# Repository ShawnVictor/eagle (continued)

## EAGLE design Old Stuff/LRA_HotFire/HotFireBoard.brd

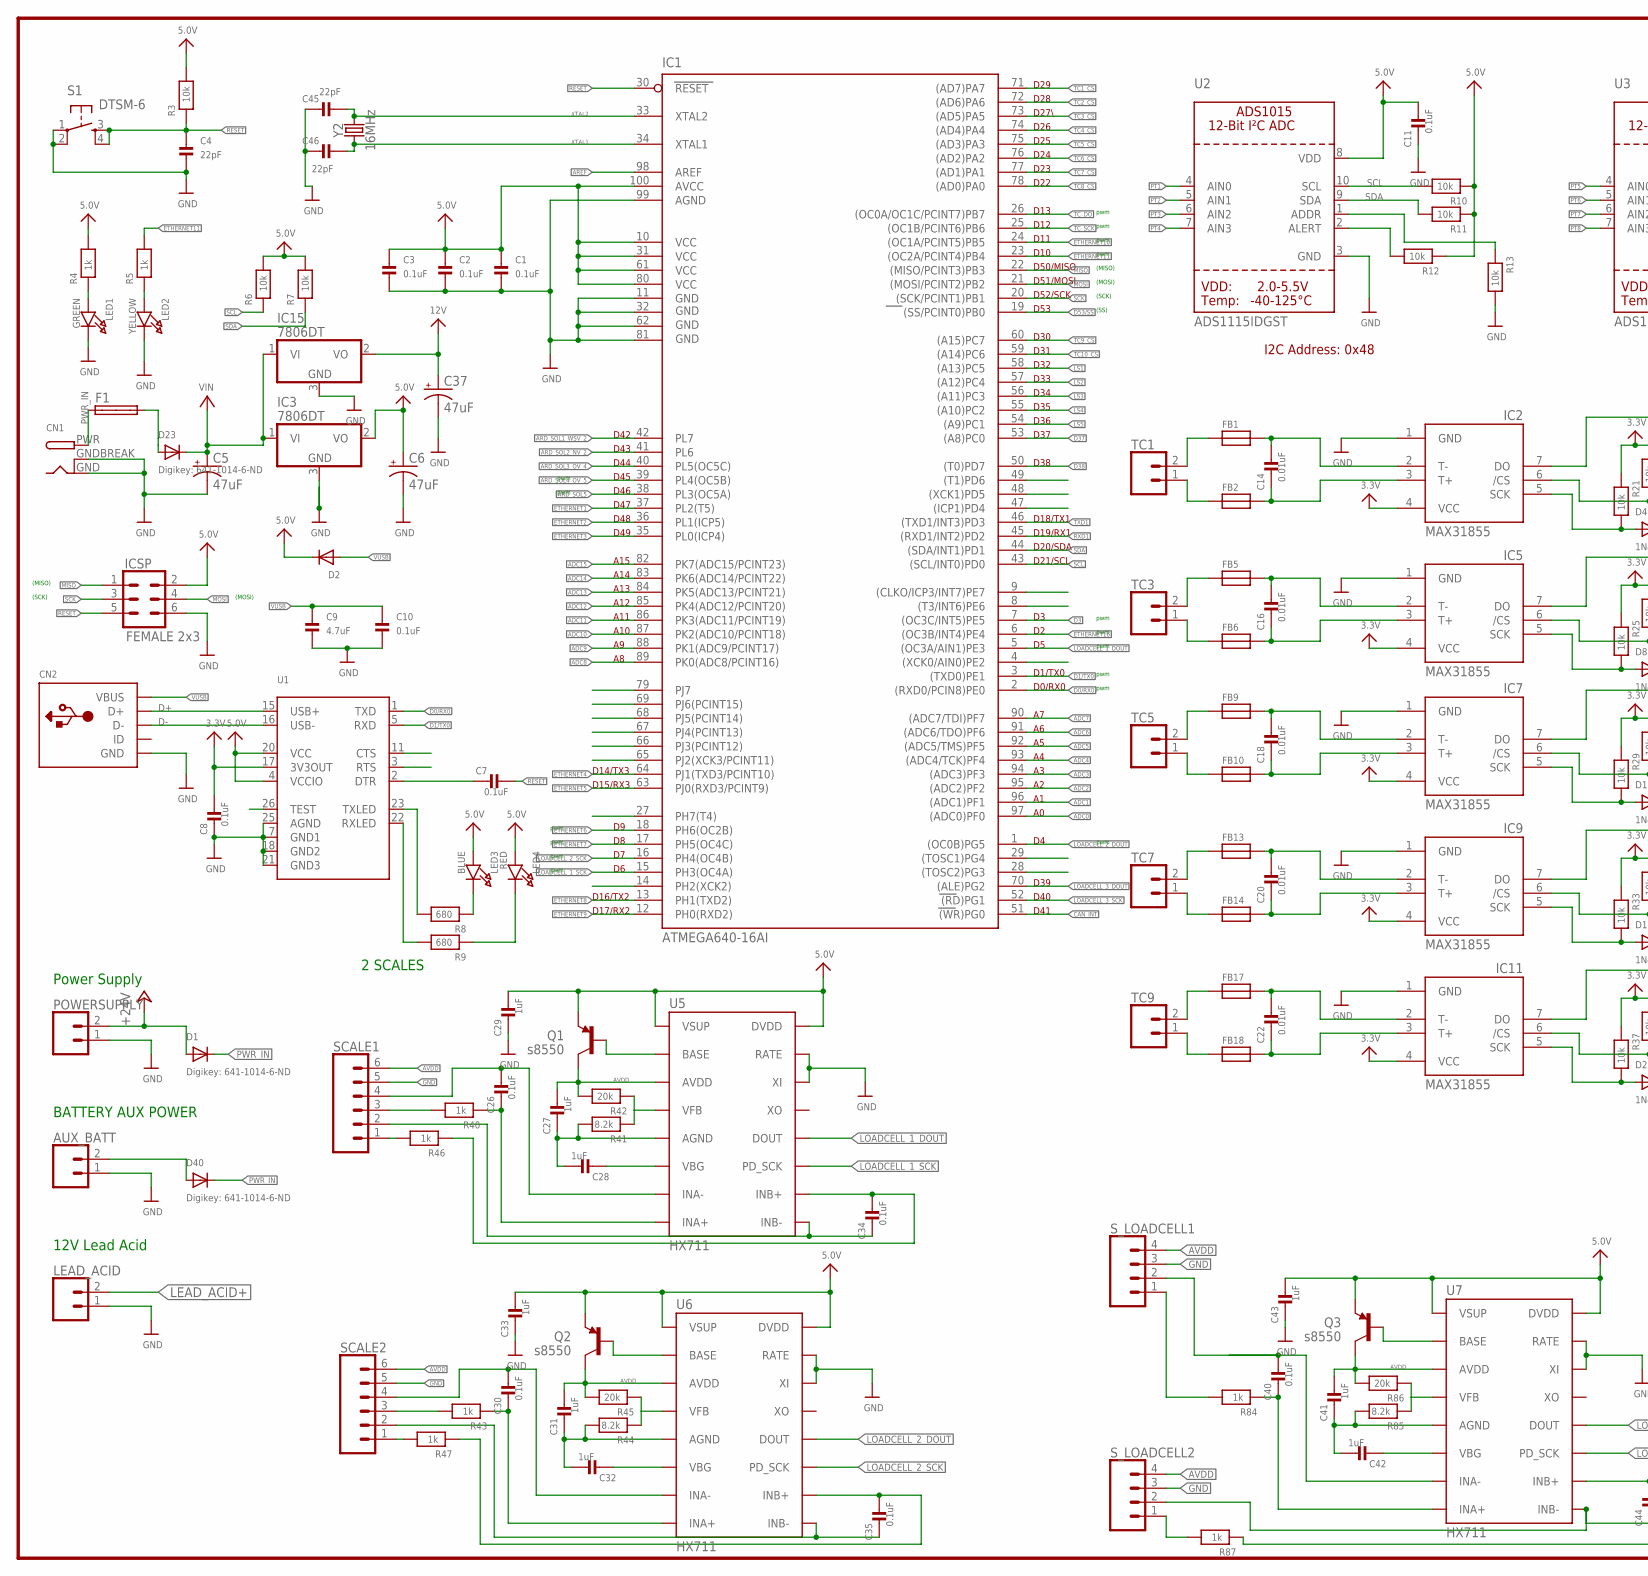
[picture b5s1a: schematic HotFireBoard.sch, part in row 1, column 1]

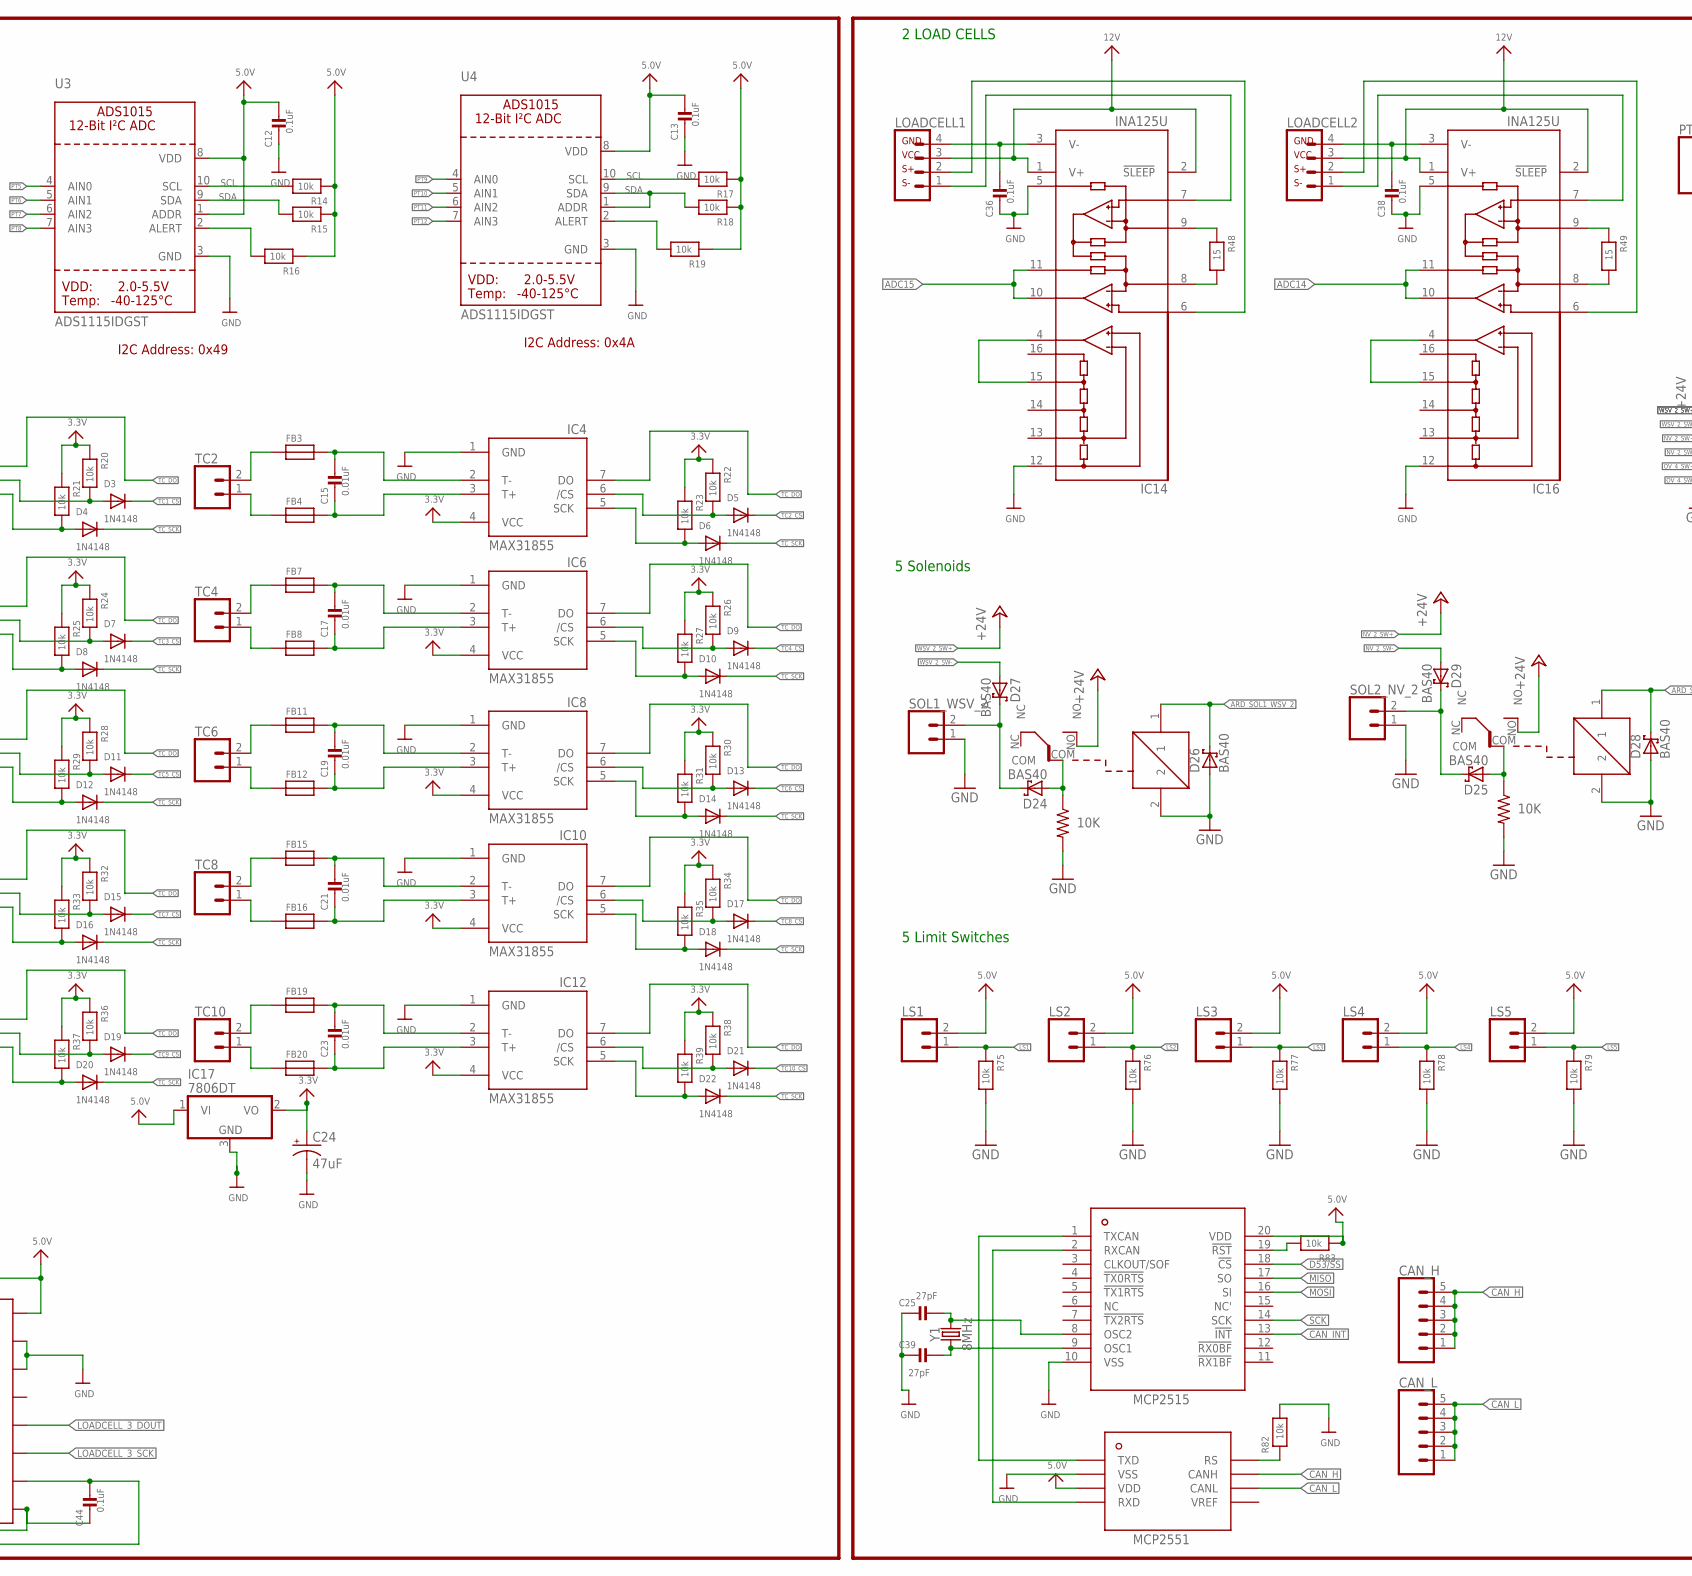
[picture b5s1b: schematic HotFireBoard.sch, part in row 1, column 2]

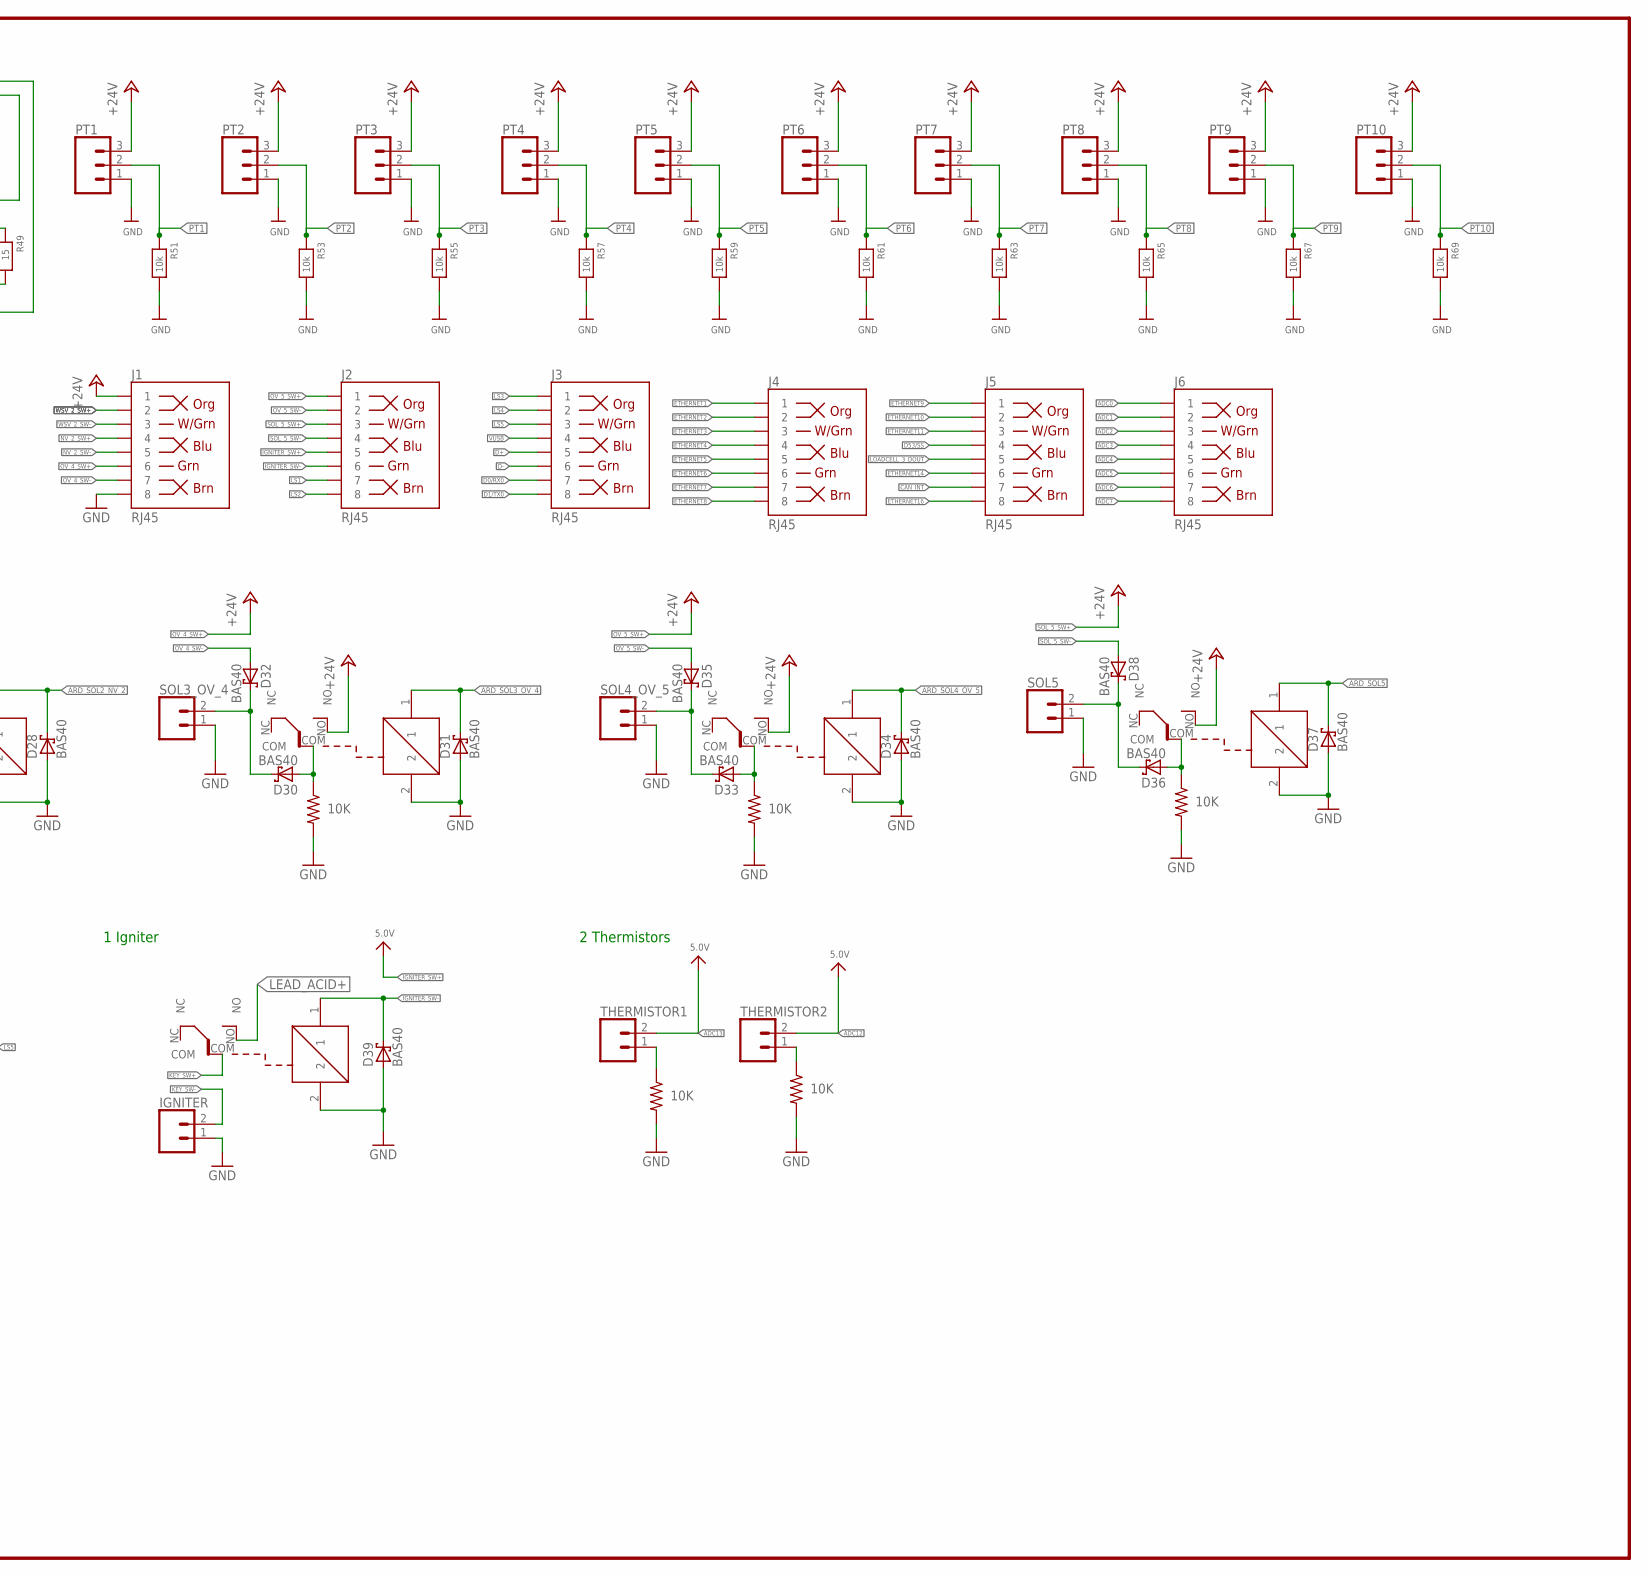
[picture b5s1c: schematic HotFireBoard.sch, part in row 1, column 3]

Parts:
AUX_BATT: CONN_02; 1X02
C1, C2, C3, C7, C8, C10, C11, C12, C13, C26, C30, C34, C35, C36, C38, C40, C44: 0.1uF; 0805
C4, C45, C46: 22pF; 0805
C5, C6, C24, C37: 47uF; PANASONIC_D
C9: 4.7uF; 0805
C14, C15, C16, C17, C18, C19, C20, C21, C22, C23: 0.01uF; 0805
C25, C39: 27pF; 0805
C27, C28, C29, C31, C32, C33, C41, C42, C43: 1uF; 0805
CAN_H: CONN_05SCREW; SCREWTERMINAL-3.5MM-5
CAN_L: CONN_05SCREW; SCREWTERMINAL-3.5MM-5
CN1: DCBARRELPTH; DCJACK_2MM_PTH
CN2: USBMINIB; USB-MINIB
D1, D23, D40: Digikey: 641-1014-6-ND; SMADIODE
D2: DIODESOD-123; SOD-123
D3, D4, D5, D6, D7, D8, D9, D10, D11, D12, D13, D14, D15, D16, D17, D18, D19, D20, D21, D22: 1N4148; SOD-123
D24, D25, D26, D27, D28, D29, D30, D31, D32, D33, D34, D35, D36, D37, D38, D39: BAS40; SOT23
F1: SHK20L
FB1, FB2, FB3, FB4, FB5, FB6, FB7, FB8, FB9, FB10, FB11, FB12, FB13, FB14, FB15, FB16, FB17, FB18, FB19, FB20: FERRITE; 0603
IC1: ATMEGA640-16AI; TQFP100
IC2, IC4, IC5, IC6, IC7, IC8, IC9, IC10, IC11, IC12: MAX31855; SO08
IC3, IC15, IC17: 7806DT; TO252
IC14, IC16: INA125U; SO16-1
ICSP: FEMALE 2x3; 2X3
IGNITER: CONN_02; 1X02
J1, J2, J3, J4, J5, J6: RJ45; RJ45-8
LEAD_ACID: CONN_02; 1X02
LED1: GREEN; CHIPLED_0805
LED2: YELLOW; CHIPLED_0805
LED3: BLUE; CHIPLED_0805
LED4: RED; CHIPLED_0805
LOADCELL1, LOADCELL2: CONN_04; 1X04
LS1, LS2, LS3, LS4, LS5: CONN_02; 1X02
POWERSUPPLY: CONN_02; 1X02
PT1, PT2, PT3, PT4, PT5, PT6, PT7, PT8, PT9, PT10: CONN_03; 1X03
Q1, Q2, Q3: s8550; TO-92
R3, R6, R7, R10, R11, R12, R13, R14, R15, R16, R17, R18, R19, R20, R21, R22, R23, R24, R25, R26, R27, R28, R29, R30, R31, R32, R33, R34, R35, R36, R37, R38, R39, R51, R53, R55, R57, R59, R61, R63, R65, R67, R69, R75, R76, R77, R78, R79, R82, R83: 10k; 0805
R4, R5, R40, R43, R46, R47, R84, R87: 1k; 0805
R8, R9: 680; 0805
R41, R44, R85: 8.2k; 0805
R42, R45, R86: 20k; 0805
R48, R49: 15; 0805
R70, R71, R72, R73, R74, R80, R81: 10K; M0805
S1: DTSM-6
SCALE1, SCALE2: CONN_06SILK_FEMALE_PTH; 1X06
SOL1_WSV_2, SOL2_NV_2, SOL3_OV_4, SOL4_OV_5, SOL5: CONN_02; 1X02
S_LOADCELL1, S_LOADCELL2: CONN_04; 1X04
TC1, TC2, TC3, TC4, TC5, TC6, TC7, TC8, TC9, TC10: CONN_02; 1X02
THERMISTOR1, THERMISTOR2: CONN_025MM; SCREWTERMINAL-5MM-2
U1: FT232RLSSOP28; SSOP28DB
U2, U3, U4: ADS1115IDGST; MSOP10
U5, U6, U7: HX711; SO16
U$6: MCP2515; TSSOP20
U$7: MCP2551; SOIC-8
U$128, U$129, U$130, U$131, U$132, U$138: RW-SH
Y1: 8MHz; HC49US
Y2: 16MHz; HC49US

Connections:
3.3V: C8.2, C24.+, IC2.4 (VCC), IC4.4 (VCC), IC5.4 (VCC), IC6.4 (VCC), IC7.4 (VCC), IC8.4 (VCC), IC9.4 (VCC), IC10.4 (VCC), IC11.4 (VCC), IC12.4 (VCC), IC17.2 (VO), R20.1, R21.1, R22.1, R23.1, R24.1, R25.1, R26.1, R27.1, R28.1, R29.1, R30.1, R31.1, R32.1, R33.1, R34.1, R35.1, R36.1, R37.1, R38.1, R39.1, U1.17 (3V3OUT)
5.0V: C1.1, C2.1, C3.1, C6.+, C11.2, C12.2, C13.2, C29.2, C33.2, C43.2, D2.C, IC1.10 (VCC), IC1.31 (VCC1), IC1.61 (VCC2), IC1.80 (VCC3), IC1.100 (AVCC), IC3.2 (VO), IC17.1 (VI), ICSP.2, LED3.A, LED4.A, LS1.2, LS2.2, LS3.2, LS4.2, LS5.2, Q1.1 (E), Q2.1 (E), Q3.1 (E), R3.2, R4.2, R6.2, R7.2, R10.1, R11.1, R12.1, R14.1, R15.1, R16.1, R17.1, R18.1, R19.1, R83.1, U1.4 (VCCIO), U1.20 (VCC), U2.8 (VDD), U3.1 (ADDR), U3.8 (VDD), U4.8 (VDD), U5.1 (VSUP), U5.16 (DVDD), U6.1 (VSUP), U6.16 (DVDD), U7.1 (VSUP), U7.16 (DVDD), U$6.20 (VDD), U$7.VDD
12V: C37.+, IC14.1 (V+), IC14.2 (!SLEEP), IC15.2 (VO), IC16.1 (V+), IC16.2 (!SLEEP), LOADCELL1.3, LOADCELL2.3
+24V: D1.A, J1.1, POWERSUPPLY.2, PT1.3, PT2.3, PT3.3, PT4.3, PT5.3, PT6.3, PT7.3, PT8.3, PT9.3, PT10.3, U$128.NO, U$129.NO, U$130.NO, U$131.NO, U$132.NO
ADC0: IC1.97 ((ADC0)PF0), J6.1
ADC1: IC1.96 ((ADC1)PF1), J6.2
ADC2: IC1.95 ((ADC2)PF2), J6.3
ADC3: IC1.94 ((ADC3)PF3), J6.4
ADC4: IC1.93 ((ADC4/TCK)PF4), J6.5
ADC5: IC1.92 ((ADC5/TMS)PF5), J6.6
ADC6: IC1.91 ((ADC6/TDO)PF6), J6.7
ADC7: IC1.90 ((ADC7/TDI)PF7), J6.8
ADC8: IC1.89 (PK0(ADC8/PCINT16))
ADC9: IC1.88 (PK1(ADC9/PCINT17))
ADC10: IC1.87 (PK2(ADC10/PCINT18))
ADC11: IC1.86 (PK3(ADC11/PCINT19))
ADC12: IC1.85 (PK4(ADC12/PCINT20)), THERMISTOR2.2
ADC13: IC1.84 (PK5(ADC13/PCINT21)), THERMISTOR1.2
ADC14: IC1.83 (PK6(ADC14/PCINT22)), IC16.10 (OUT), IC16.11 (SENSE)
ADC15: IC1.82 (PK7(ADC15/PCINT23)), IC14.10 (OUT), IC14.11 (SENSE)
ARD_SOL1_WSV_2: D26.3 (C), IC1.42 (PL7), U$128.1
ARD_SOL2_NV_2: D28.3 (C), IC1.41 (PL6), U$129.1
ARD_SOL3_OV_4: D31.3 (C), IC1.40 (PL5(OC5C)), U$130.1
ARD_SOL4_OV_5: D34.3 (C), IC1.39 (PL4(OC5B)), U$131.1
ARD_SOL5: D37.3 (C), IC1.38 (PL3(OC5A)), U$132.1
AREF: IC1.98 (AREF)
AVDD: C27.2, C31.2, C41.2, Q1.3 (C), Q2.3 (C), Q3.3 (C), R42.2, R45.2, R86.2, SCALE1.6, SCALE2.6, S_LOADCELL1.4, S_LOADCELL2.4, U5.3 (AVDD), U6.3 (AVDD), U7.3 (AVDD)
CAN_H: CAN_H.1, CAN_H.2, CAN_H.3, CAN_H.4, CAN_H.5, U$7.CANH
CAN_INT: IC1.51 ((WR)PG0), J5.7, U$6.13 (!INT)
CAN_L: CAN_L.1, CAN_L.2, CAN_L.3, CAN_L.4, CAN_L.5, U$7.CANL
D0/RX0: IC1.2 ((RXD0/PCIN8)PE0), J3.7, U1.1 (TXD)
D1/TX0: IC1.3 ((TXD0)PE1), J3.8, U1.5 (RXD)
D3: IC1.7 ((OC3C/INT5)PE5)
D37: IC1.53 ((A8)PC0)
D38: IC1.50 ((T0)PD7)
D53/SS: IC1.19 ((SS/PCINT0)PB0), J5.4, U$6.18 (!CS)
D+: CN2.D+, J3.5, U1.15 (USB+)
D-: CN2.D-, J3.6, U1.16 (USB-)
ETHERNET1: IC1.37 (PL2(T5)), J4.1
ETHERNET2: IC1.36 (PL1(ICP5)), J4.2
ETHERNET3: IC1.35 (PL0(ICP4)), J4.3
ETHERNET4: IC1.64 (PJ1(TXD3/PCINT10)), J4.4
ETHERNET5: IC1.63 (PJ0(RXD3/PCINT9)), J4.5
ETHERNET6: IC1.18 (PH6(OC2B)), J4.6
ETHERNET7: IC1.17 (PH5(OC4C)), J4.7
ETHERNET8: IC1.13 (PH1(TXD2)), J4.8
ETHERNET9: IC1.12 (PH0(RXD2)), J5.1
ETHERNET10: IC1.24 ((OC1A/PCINT5)PB5), J5.2
ETHERNET11: IC1.23 ((OC2A/PCINT4)PB4), J5.3, R5.2
ETHERNET14: J5.6
ETHERNET16: IC1.6 ((OC3B/INT4)PE4), J5.8
GND: AUX_BATT.1, C1.2, C2.2, C3.2, C4.2, C5.-, C6.-, C8.1, C9.1, C10.1, C11.1, C12.1, C13.1, C24.-, C25.1, C29.1, C33.1, C36.1, C37.-, C38.1, C39.1, C43.1, C45.1, C46.1, CN1.GND, CN1.GNDBREAK, CN2.GND, D26.1 (A), D28.1 (A), D31.1 (A), D34.1 (A), D37.1 (A), D39.1 (A), IC1.11 (GND), IC1.32 (GND1), IC1.62 (GND2), IC1.81 (GND3), IC1.99 (AGND), IC2.1 (GND), IC3.3 (GND), IC4.1 (GND), IC5.1 (GND), IC6.1 (GND), IC7.1 (GND), IC8.1 (GND), IC9.1 (GND), IC10.1 (GND), IC11.1 (GND), IC12.1 (GND), IC14.5 (REF), IC14.12 (REFCOM), IC15.3 (GND), IC16.5 (REF), IC16.12 (REFCOM), IC17.3 (GND), ICSP.6, IGNITER.1, J1.8, LEAD_ACID.1, LED1.C, LED2.C, POWERSUPPLY.1, PT1.1, PT2.1, PT3.1, PT4.1, PT5.1, PT6.1, PT7.1, PT8.1, PT9.1, PT10.1, R13.2, R51.2, R53.2, R55.2, R57.2, R59.2, R61.2, R63.2, R65.2, R67.2, R69.2, R70.2, R71.2, R72.2, R73.2, R74.2, R75.2, R76.2, R77.2, R78.2, R79.2, R80.2, R81.2, R82.2, S1.1, S1.2, SCALE1.5, SCALE2.5, SOL1_WSV_2.1, SOL2_NV_2.1, SOL3_OV_4.1, SOL4_OV_5.1, SOL5.1, S_LOADCELL1.3, S_LOADCELL2.3, U1.7 (GND1), U1.18 (GND2), U1.21 (GND3), U1.25 (AGND), U2.3 (GND), U3.3 (GND), U4.3 (GND), U5.14 (XI), U5.15 (RATE), U6.14 (XI), U6.15 (RATE), U7.14 (XI), U7.15 (RATE), U$6.10 (VSS), U$7.VSS, U$128.2, U$129.2, U$130.2, U$131.2, U$132.2, U$138.2
IGNITER_SW+: J2.5
IGNITER_SW-: D39.3 (C), J2.6, U$138.1
KEY_SW+: U$138.COM
KEY_SW-: IGNITER.2
LEAD_ACID+: LEAD_ACID.2, U$138.NO
LOADCELL_1_DOUT: IC1.5 ((OC3A/AIN1)PE3), U5.12 (DOUT)
LOADCELL_1_SCK: IC1.15 (PH3(OC4A)), U5.11 (PD_SCK)
LOADCELL_2_DOUT: IC1.1 ((OC0B)PG5), U6.12 (DOUT)
LOADCELL_2_SCK: IC1.16 (PH4(OC4B)), U6.11 (PD_SCK)
LOADCELL_3_DOUT: IC1.70 ((ALE)PG2), J5.5, U7.12 (DOUT)
LOADCELL_3_SCK: IC1.52 ((RD)PG1), U7.11 (PD_SCK)
LS1: IC1.58 ((A13)PC5), J2.7, LS1.1, R75.1
LS2: IC1.57 ((A12)PC4), J2.8, LS2.1, R76.1
LS3: IC1.56 ((A11)PC3), J3.1, LS3.1, R77.1
LS4: IC1.55 ((A10)PC2), J3.2, LS4.1, R78.1
LS5: IC1.54 ((A9)PC1), J3.3, LS5.1, R79.1
MISO: IC1.22 ((MISO/PCINT3)PB3), ICSP.1, U$6.17 (SO)
MOSI: IC1.21 ((MOSI/PCINT2)PB2), ICSP.4, U$6.16 (SI)
unnamed: U$6.1 (TXCAN), U$7.TXD
unnamed: U$6.2 (RXCAN), U$7.RXD
unnamed: C25.2, U$6.8 (OSC2), Y1.2
unnamed: LED1.A, R4.1
unnamed: LED2.A, R5.1
unnamed: LED3.C, R8.1
unnamed: R9.2, U1.22 (RXLED)
unnamed: R8.2, U1.23 (TXLED)
unnamed: LED4.C, R9.1
unnamed: C14.1, FB2.2, IC2.3 (T+)
unnamed: C7.1, U1.2 (DTR)
unnamed: C14.2, FB1.2, IC2.2 (T-)
unnamed: R82.1, U$7.RS
unnamed: D3.A, IC2.6 (/CS), R20.2
unnamed: R83.2, U$6.19 (!RST)
unnamed: C39.2, U$6.9 (OSC1), Y1.1
unnamed: R84.2, S_LOADCELL1.1
unnamed: R12.2, U2.2 (ALERT)
unnamed: C40.1, R84.1, U7.8 (INA+)
unnamed: R16.2, U3.2 (ALERT)
unnamed: R13.1, U2.1 (ADDR)
unnamed: C40.2, S_LOADCELL1.2, U7.7 (INA-)
unnamed: FB1.1, TC1.2
unnamed: R19.2, U4.2 (ALERT)
unnamed: C41.1, C42.2, R85.2, U7.5 (AGND)
unnamed: FB2.1, TC1.1
unnamed: D4.A, IC2.5 (SCK), R21.2
unnamed: C15.2, FB3.2, IC4.2 (T-)
unnamed: C42.1, U7.6 (VBG)
unnamed: R85.1, R86.1, U7.4 (VFB)
unnamed: C15.1, FB4.2, IC4.3 (T+)
unnamed: FB3.1, TC2.2
unnamed: FB4.1, TC2.1
unnamed: D5.A, IC4.6 (/CS), R22.2
unnamed: D6.A, IC4.5 (SCK), R23.2
unnamed: C16.2, FB5.2, IC5.2 (T-)
unnamed: C16.1, FB6.2, IC5.3 (T+)
unnamed: FB5.1, TC3.2
unnamed: FB6.1, TC3.1
unnamed: D7.A, IC5.6 (/CS), R24.2
unnamed: D8.A, IC5.5 (SCK), R25.2
unnamed: C17.2, FB7.2, IC6.2 (T-)
unnamed: C17.1, FB8.2, IC6.3 (T+)
unnamed: FB7.1, TC4.2
unnamed: FB8.1, TC4.1
unnamed: D9.A, IC6.6 (/CS), R26.2
unnamed: D10.A, IC6.5 (SCK), R27.2
unnamed: C18.2, FB9.2, IC7.2 (T-)
unnamed: C18.1, FB10.2, IC7.3 (T+)
unnamed: FB9.1, TC5.2
unnamed: FB10.1, TC5.1
unnamed: D11.A, IC7.6 (/CS), R28.2
unnamed: D12.A, IC7.5 (SCK), R29.2
unnamed: C19.2, FB11.2, IC8.2 (T-)
unnamed: C19.1, FB12.2, IC8.3 (T+)
unnamed: FB11.1, TC6.2
unnamed: FB12.1, TC6.1
unnamed: D13.A, IC8.6 (/CS), R30.2
unnamed: D14.A, IC8.5 (SCK), R31.2
unnamed: C20.2, FB13.2, IC9.2 (T-)
unnamed: C20.1, FB14.2, IC9.3 (T+)
unnamed: FB13.1, TC7.2
unnamed: FB14.1, TC7.1
unnamed: D15.A, IC9.6 (/CS), R32.2
unnamed: D16.A, IC9.5 (SCK), R33.2
unnamed: C21.2, FB15.2, IC10.2 (T-)
unnamed: C21.1, FB16.2, IC10.3 (T+)
unnamed: FB15.1, TC8.2
unnamed: FB16.1, TC8.1
unnamed: D17.A, IC10.6 (/CS), R34.2
unnamed: D18.A, IC10.5 (SCK), R35.2
unnamed: C22.2, FB17.2, IC11.2 (T-)
unnamed: C22.1, FB18.2, IC11.3 (T+)
unnamed: FB17.1, TC9.2
unnamed: FB18.1, TC9.1
unnamed: D19.A, IC11.6 (/CS), R36.2
unnamed: D20.A, IC11.5 (SCK), R37.2
unnamed: C23.2, FB19.2, IC12.2 (T-)
unnamed: C23.1, FB20.2, IC12.3 (T+)
unnamed: FB19.1, TC10.2
unnamed: FB20.1, TC10.1
unnamed: D21.A, IC12.6 (/CS), R38.2
unnamed: D22.A, IC12.5 (SCK), R39.2
unnamed: R40.2, SCALE1.3
unnamed: C26.1, R40.1, U5.8 (INA+)
unnamed: C26.2, SCALE1.4, U5.7 (INA-)
unnamed: R43.2, SCALE2.3
unnamed: C27.1, C28.2, R41.2, U5.5 (AGND)
unnamed: C28.1, U5.6 (VBG)
unnamed: R41.1, R42.1, U5.4 (VFB)
unnamed: Q1.2 (B), U5.2 (BASE)
unnamed: C30.1, R43.1, U6.8 (INA+)
unnamed: C30.2, SCALE2.4, U6.7 (INA-)
unnamed: C31.1, C32.2, R44.2, U6.5 (AGND)
unnamed: C32.1, U6.6 (VBG)
unnamed: R44.1, R45.1, U6.4 (VFB)
unnamed: Q2.2 (B), U6.2 (BASE)
unnamed: C34.1, SCALE1.2, U5.9 (INB-)
unnamed: C34.2, R46.1, U5.10 (INB+)
unnamed: R46.2, SCALE1.1
unnamed: C35.1, SCALE2.2, U6.9 (INB-)
unnamed: C35.2, R47.1, U6.10 (INB+)
unnamed: R47.2, SCALE2.1
unnamed: C36.2, IC14.3 (V-), LOADCELL1.4
unnamed: C38.2, IC16.3 (V-), LOADCELL2.4
unnamed: IC14.9 (RG), R48.1
unnamed: IC14.8 (RG), R48.2
unnamed: IC14.6 (+IN), LOADCELL1.2
unnamed: IC16.9 (RG), R49.1
unnamed: IC16.8 (RG), R49.2
unnamed: IC16.6 (+IN), LOADCELL2.2
unnamed: IC14.4 (REFOUT), IC14.15 (REF5)
unnamed: IC14.7 (-IN), LOADCELL1.1
unnamed: IC16.4 (REFOUT), IC16.15 (REF5)
unnamed: IC16.7 (-IN), LOADCELL2.1
unnamed: D24.3 (C), D27.3 (C), SOL1_WSV_2.2
unnamed: D24.1 (A), R70.1, U$128.COM
unnamed: D25.3 (C), D29.3 (C), SOL2_NV_2.2
unnamed: D25.1 (A), R71.1, U$129.COM
unnamed: D30.3 (C), D32.3 (C), SOL3_OV_4.2
unnamed: D30.1 (A), R72.1, U$130.COM
unnamed: D33.3 (C), D35.3 (C), SOL4_OV_5.2
unnamed: D33.1 (A), R73.1, U$131.COM
unnamed: D36.3 (C), D38.3 (C), SOL5.2
unnamed: D36.1 (A), R74.1, U$132.COM
unnamed: R80.1, THERMISTOR1.1
unnamed: Q3.2 (B), U7.2 (BASE)
unnamed: C44.1, S_LOADCELL2.2, U7.9 (INB-)
unnamed: R81.1, THERMISTOR2.1
unnamed: C44.2, R87.1, U7.10 (INB+)
unnamed: R87.2, S_LOADCELL2.1
unnamed: D23.A, F1.2A
unnamed: AUX_BATT.2, D40.A
NV_2_SW+: J1.4
NV_2_SW-: D29.1 (A), J1.5
OV_4_SW+: J1.6
OV_4_SW-: D32.1 (A), J1.7
OV_5_SW+: J2.1
OV_5_SW-: D35.1 (A), J2.2
PT1: PT1.2, R51.1, U2.4 (AIN0)
PT2: PT2.2, R53.1, U2.5 (AIN1)
PT3: PT3.2, R55.1, U2.6 (AIN2)
PT4: PT4.2, R57.1, U2.7 (AIN3)
PT5: PT5.2, R59.1, U3.4 (AIN0)
PT6: PT6.2, R61.1, U3.5 (AIN1)
PT7: PT7.2, R63.1, U3.6 (AIN2)
PT8: PT8.2, R65.1, U3.7 (AIN3)
PT9: PT9.2, R67.1, U4.4 (AIN0)
PT10: PT10.2, R69.1, U4.5 (AIN1)
PT11: U4.6 (AIN2)
PT12: U4.7 (AIN3)
PWR_IN: CN1.PWR, D1.C, D40.C, F1.1A
RESET: C4.1, C7.2, IC1.30 (RESET), ICSP.5, R3.1, S1.3, S1.4
RXD1: IC1.45 ((RXD1/INT2)PD2)
SCK: IC1.20 ((SCK/PCINT1)PB1), ICSP.3, U$6.14 (SCK)
SCL: IC1.43 ((SCL/INT0)PD0), R6.1, R10.2, R14.2, R17.2, U2.10 (SCL), U3.10 (SCL), U4.10 (SCL)
SDA: IC1.44 ((SDA/INT1)PD1), R7.1, R11.2, R15.2, R18.2, U2.9 (SDA), U3.9 (SDA), U4.1 (ADDR), U4.9 (SDA)
SOL_5_SW+: J2.3
SOL_5_SW-: D38.1 (A), J2.4
TC1_CS: D3.C, IC1.71 ((AD7)PA7)
TC2_CS: D5.C, IC1.72 ((AD6)PA6)
TC3_CS: D7.C, IC1.73 ((AD5)PA5)
TC4_CS: D9.C, IC1.74 ((AD4)PA4)
TC5_CS: D11.C, IC1.75 ((AD3)PA3)
TC6_CS: D13.C, IC1.76 ((AD2)PA2)
TC7_CS: D15.C, IC1.77 ((AD1)PA1)
TC8_CS: D17.C, IC1.78 ((AD0)PA0)
TC9_CS: D19.C, IC1.60 ((A15)PC7)
TC10_CS: D21.C, IC1.59 ((A14)PC6)
TC_DO: IC1.26 ((OC0A/OC1C/PCINT7)PB7), IC2.7 (DO), IC4.7 (DO), IC5.7 (DO), IC6.7 (DO), IC7.7 (DO), IC8.7 (DO), IC9.7 (DO), IC10.7 (DO), IC11.7 (DO), IC12.7 (DO)
TC_SCK: D4.C, D6.C, D8.C, D10.C, D12.C, D14.C, D16.C, D18.C, D20.C, D22.C, IC1.25 ((OC1B/PCINT6)PB6)
TXD1: IC1.46 ((TXD1/INT3)PD3)
VIN: C5.+, D23.C, IC3.1 (VI), IC15.1 (VI)
VUSB: C9.2, C10.2, CN2.VBUS, D2.A, J3.4
WSV_2_SW+: J1.2
WSV_2_SW-: D27.1 (A), J1.3
XTAL1: C46.2, IC1.34 (XTAL1), Y2.1
XTAL2: C45.2, IC1.33 (XTAL2), Y2.2

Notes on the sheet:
pwm
(SS)
(SCK)
(MOSI)
(MISO)
I2C Address: 0x48
I2C Address: 0x49
I2C Address: 0x4A
BATTERY AUX POWER
5 Solenoids
5 Limit Switches
1 Igniter
2 SCALES
2 Thermistors
GND
VCC
2 LOAD CELLS
D42
D43
D44
D45
D46
D47
D48
D49
A15
A14
A13
A12
A11
A10
D14/TX3
D15/RX3
D16/TX2
D17/RX2
D29
D28
D27\
D26
D25

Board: 2 copper layers, 276 parts (0 on the bottom side), 227 nets, no tracks yet.

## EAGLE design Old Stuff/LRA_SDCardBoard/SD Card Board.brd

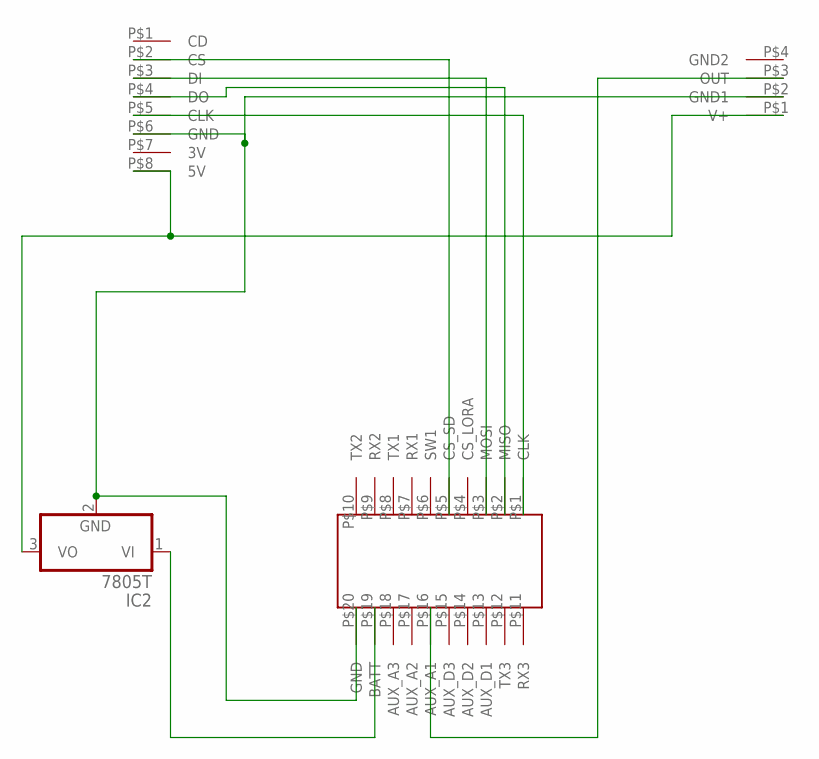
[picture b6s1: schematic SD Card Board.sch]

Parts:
IC2: 7805T; TO220H
U$1: SMALLHEADERPACKAGE
U$2: SDCARDREADER; SDCARDBOARD
U$3: THERMOCOUPLE; THERMOBOARD

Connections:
unnamed: IC2.1 (VI), U$1.P$19 (BATT)
unnamed: IC2.3 (VO), U$2.P$8 (5V), U$3.P$1 (V+)
unnamed: IC2.2 (GND), U$1.P$20 (GND), U$2.P$6 (GND), U$3.P$2 (GND1)
unnamed: U$1.P$1 (CLK), U$2.P$5 (CLK)
unnamed: U$1.P$16 (AUX_A1), U$3.P$3 (OUT)
unnamed: U$1.P$2 (MISO), U$2.P$4 (DO)
unnamed: U$1.P$3 (MOSI), U$2.P$3 (DI)
unnamed: U$1.P$5 (CS_SD), U$2.P$2 (CS)

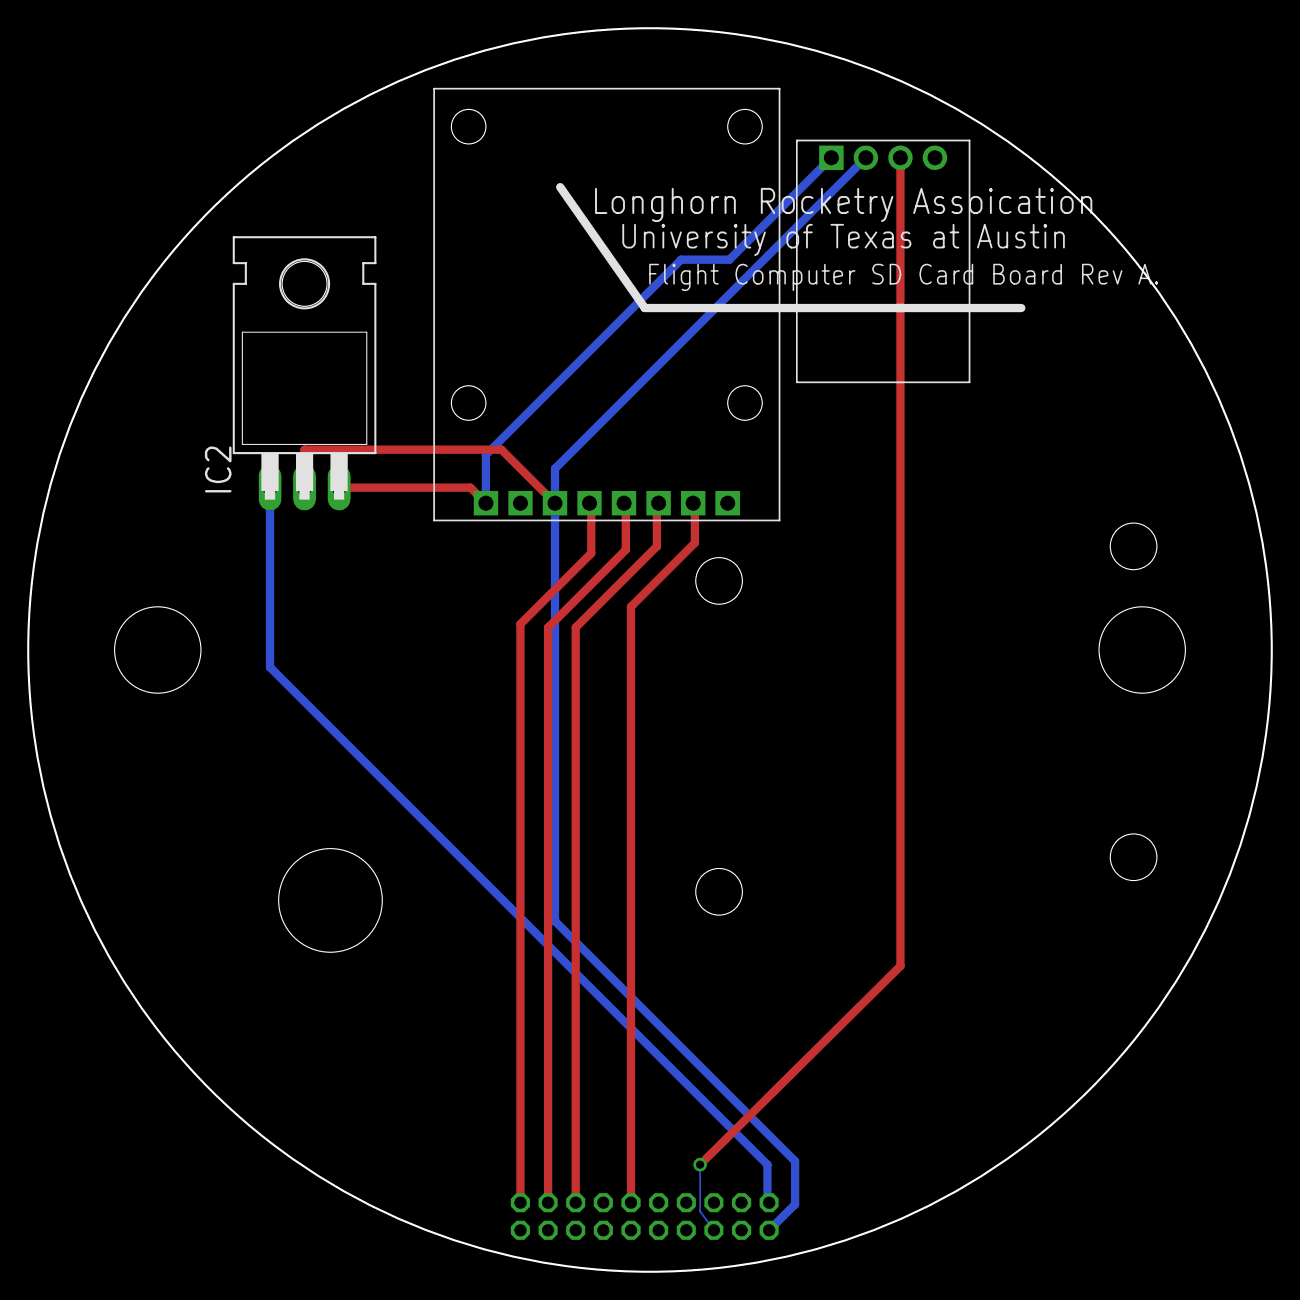
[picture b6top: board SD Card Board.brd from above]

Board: 2 copper layers, 91.4 x 91.4 mm, 4 parts (0 on the bottom side), 8 nets.

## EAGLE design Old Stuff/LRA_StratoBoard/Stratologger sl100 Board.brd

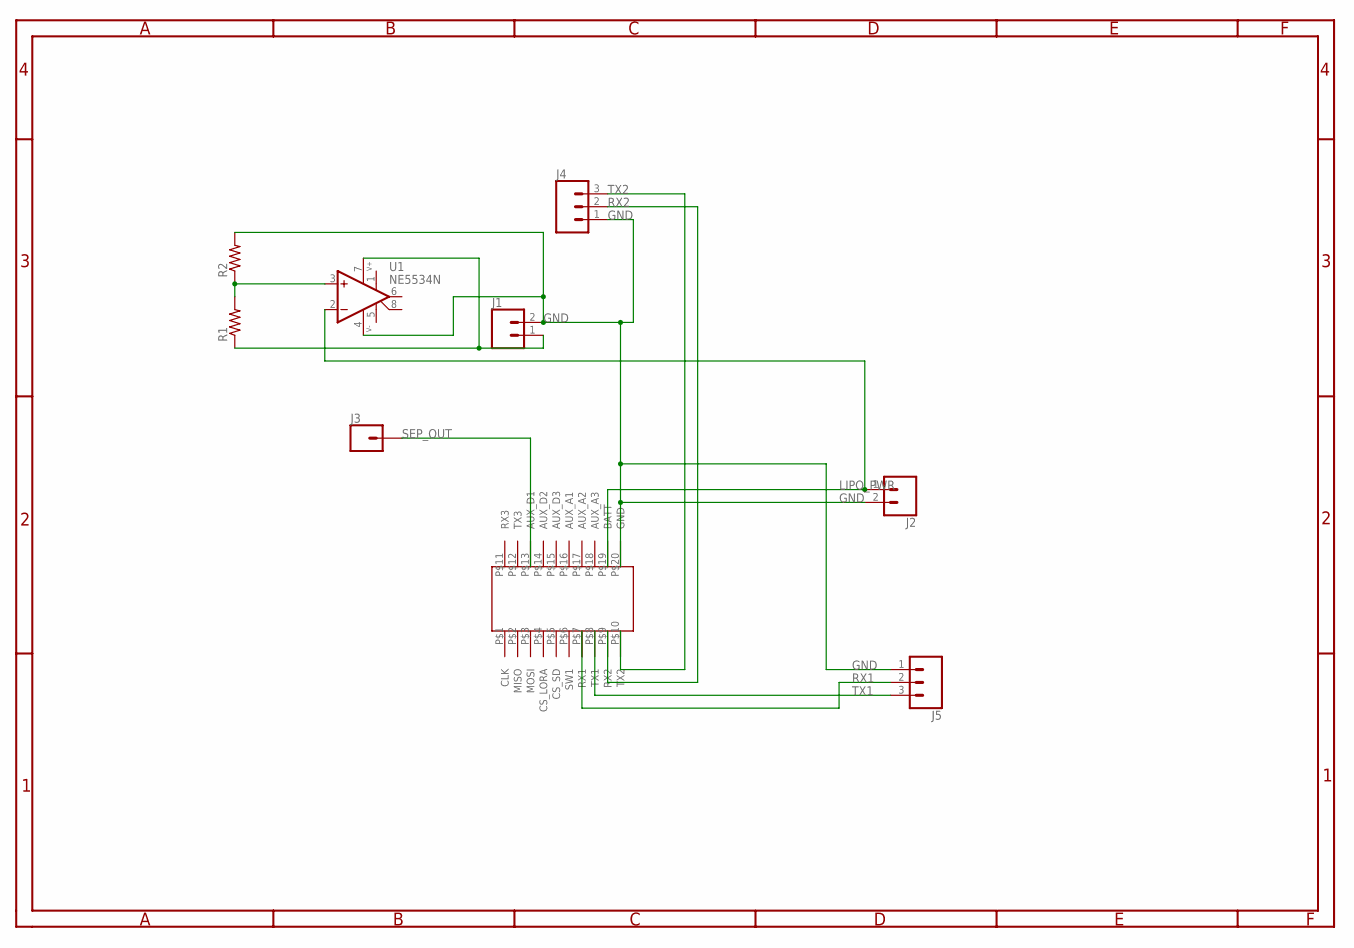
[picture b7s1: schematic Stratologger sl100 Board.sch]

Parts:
J1, J2: CONN_02; 1X02
J3: CONN_01; 1X01
J4, J5: CONN_03; 1X03
R1, R2: R-US_0207/12; 0207/12
U1: NE5534N; DIL08
U$2: STRATOLOGGER
U$3: SMALLHEADERPACKAGE

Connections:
GND: J1.2, J2.2, J4.1, J5.1, R2.2, U1.4 (V-), U$3.P$20 (GND)
LIPO_PWR: J2.1, U1.2 (-IN), U$3.P$19 (BATT)
unnamed: J1.1, R1.1, U1.7 (V+)
unnamed: R1.2, R2.1, U1.3 (+IN)
RX1: J5.2, U$3.P$7 (RX1)
RX2: J4.2, U$3.P$9 (RX2)
SEP_OUT: J3.1, U$3.P$13 (AUX_D1)
TX1: J5.3, U$3.P$8 (TX1)
TX2: J4.3, U$3.P$10 (TX2)

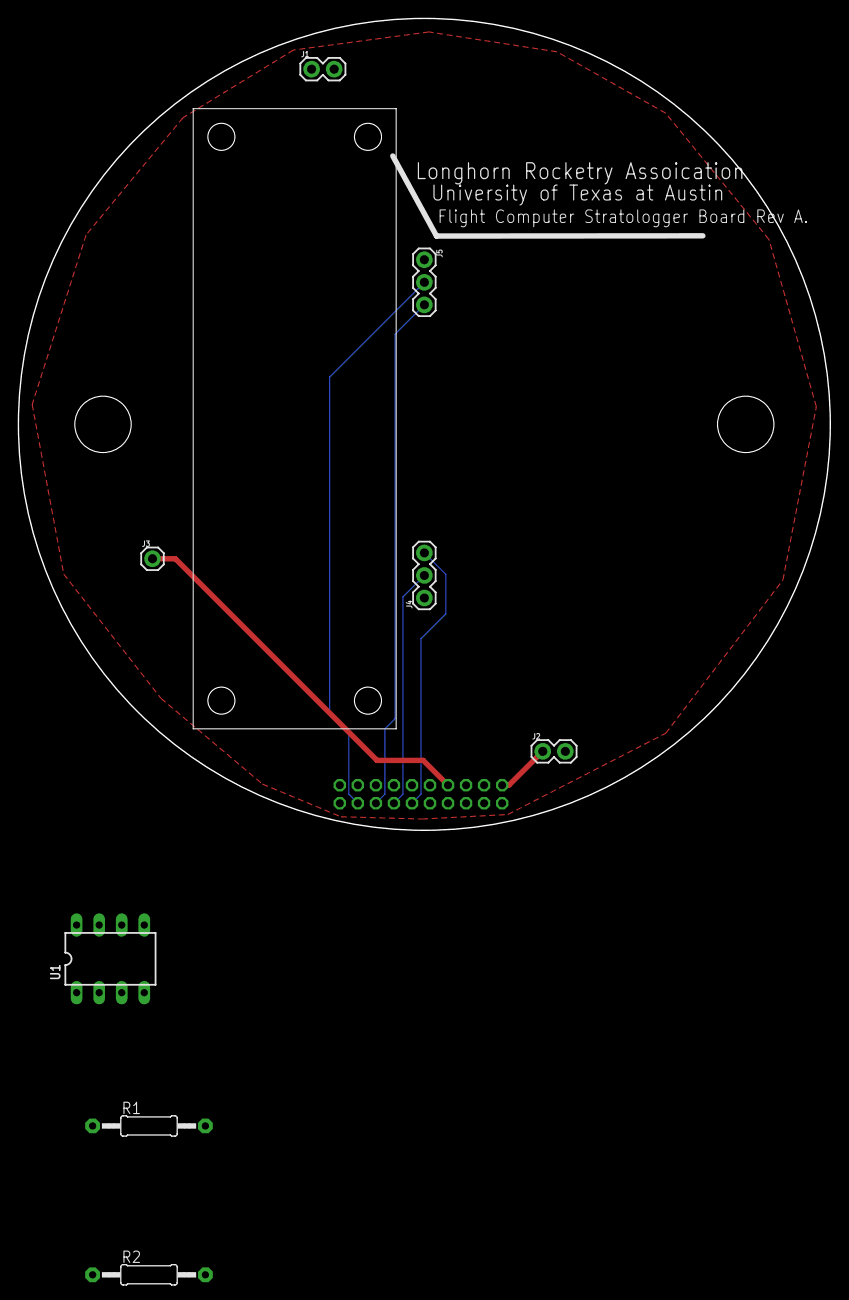
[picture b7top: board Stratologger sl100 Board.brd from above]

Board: 2 copper layers, 91.4 x 91.4 mm, 10 parts (0 on the bottom side), 9 nets.
